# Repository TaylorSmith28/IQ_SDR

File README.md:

# IQ_SDR
The goal of this project was to design a software defined radio (SDR) reciever that operated in the range of 7-12 MHz. This project was conducted with my partner Cadyn Maddocks as part of Walla Walla University's Electronics II course.
## Design Goals
The following design objectives were given for this project:
1. Minimum discernible signal less than 1uV
2. Visible image rejection through quisk
3. Low noise figure
4. Low Cost ($25 budget)
Cadyn Maddocks and I set additional design obectives in order to aid in the design process:
1. Operate in a Frequency Range of 7-12MHz
2. Modulation Type: Short Wave
3. Size of 10 cm by 10 cm
4. Weight of less than 2 pounds
5. Power Requirement of 5V
6. Use of Butterworth Bandpass Filter
7. Use the Raspberry Pi Pico
## Overview
The Software Defined Radio (SDR) reciever has three ports: antenna, USB, and audio jack. The input from the antenna gets filtered, mixed, and then the desired signal is then amplified. The input from the USB to the Raspberry Pi Pico powers the radio and operates the oscillator. The audio jack is connected to a sound card that is attached to a computer where the software demodulates the signal into recognizable audio. Mixing is accomplished via the Raspberry Pi Pico, with ported arduino code from Dr. Rob Frohne. This code interacts with Quisk, a software that controls the reciever through the Raspberry Pi. Quisk should allow the radio to be tuned to certain frequency but this was not accomplished due to issues from porting the arduino code over to the Raspberry Pi Pico. The total cost of this project was about $25.
# Version 6 Design

Shown above is the design schematic for the SDR. More details will be given down below about each section of the schematic. This includes a 12MHz BandPass Filter, Tayloe Mixer, Oscillator, Voltage Smoother, LM4562MA Power Supply, and a Multiple Feedback Lowpass Filter and Amplifier.
## Bandpass Filter

Shown above is a 7-12MHz, 3rd order, series first, Butterworth, bandpass filter. The above filter was designed using the LC Filter Design Tool found here: https://rf-tools.com/lc-filter/
## DC Voltage Smoother

In order to limit noise into our radio a 5V voltage smoother was used before entering the bandpass filter.
## Oscillator

For the design of our radio we used a Si5351A-B-GT Oscillator.
## Tayloe Mixer and Multiple Feedback Lowpass Filter and Amplifer

The SDR uses a SN74CBT3253 Tayloe Mixer that leads into a Multiple Feedback Lowpass Filter and Amplifer. The amplifier employs the use of two LMH4562MA op amps, and has a cutoff frequency around 100kHz.
## Raspberry Pi Pico

Shown above is the Raspberry Pi Pico and the pins used to drive the SDR.
# Simulations
## Multiple Feedback Amplifier Simulation

Shown here is an LTSpice simulation for our Multiple Feedback Amplifier. The simulation shows the amplifier's response between 100Hz to 100MHz.
## 7-12MHz Bandpass Filter

Shown above is a simulation of the 7-12MHz Bandpass Filter. From the simulation, you can see that the response allows signals to pass from approximately 7-12MHz.
# PCB Design

The board shown above was sourced from JLCPCB. Certain design principles were taken into consideration when coming up with the initial design of the board, such as:
1. Avoidance of ground loops
2. Distance between power supply and Antenna
3. Use of a Voltage Smoother
# Quisk Setup
Quisk was downloaded from http://www.james.ahlstrom.name/quisk/ on to a laptop was able to be loaded onto the Raspberry Pi Pico. Quisk was then configured to operating on COM3, the respective port that communicated with the Raspberry Pi. Upon opening Quisk, a new SoftRock Fixed Radio was created and configured to use the appropriate sound card input. The hardware file path was also changed to quisk_conf_openradio.py to use the code that was ported from Dr. Frohne's orignial arduino code.
# Results

Looking at the results above, image rejection can still be seen around 1 microvolt at a 10MHz frequency. This was the best image rejection that we were able to obtain. Using the antenna on top of the Kretschmar roof, we were able to obtain a clearly discernible signal from a religious radio station. Thank the Lord. 
# Credits
Huge credits go to Cadyn Maddocks, my teammate who helped tremendoulsy on this project

Also thanks to Professor Rob Frohne, for without his help this project would not have been possible.

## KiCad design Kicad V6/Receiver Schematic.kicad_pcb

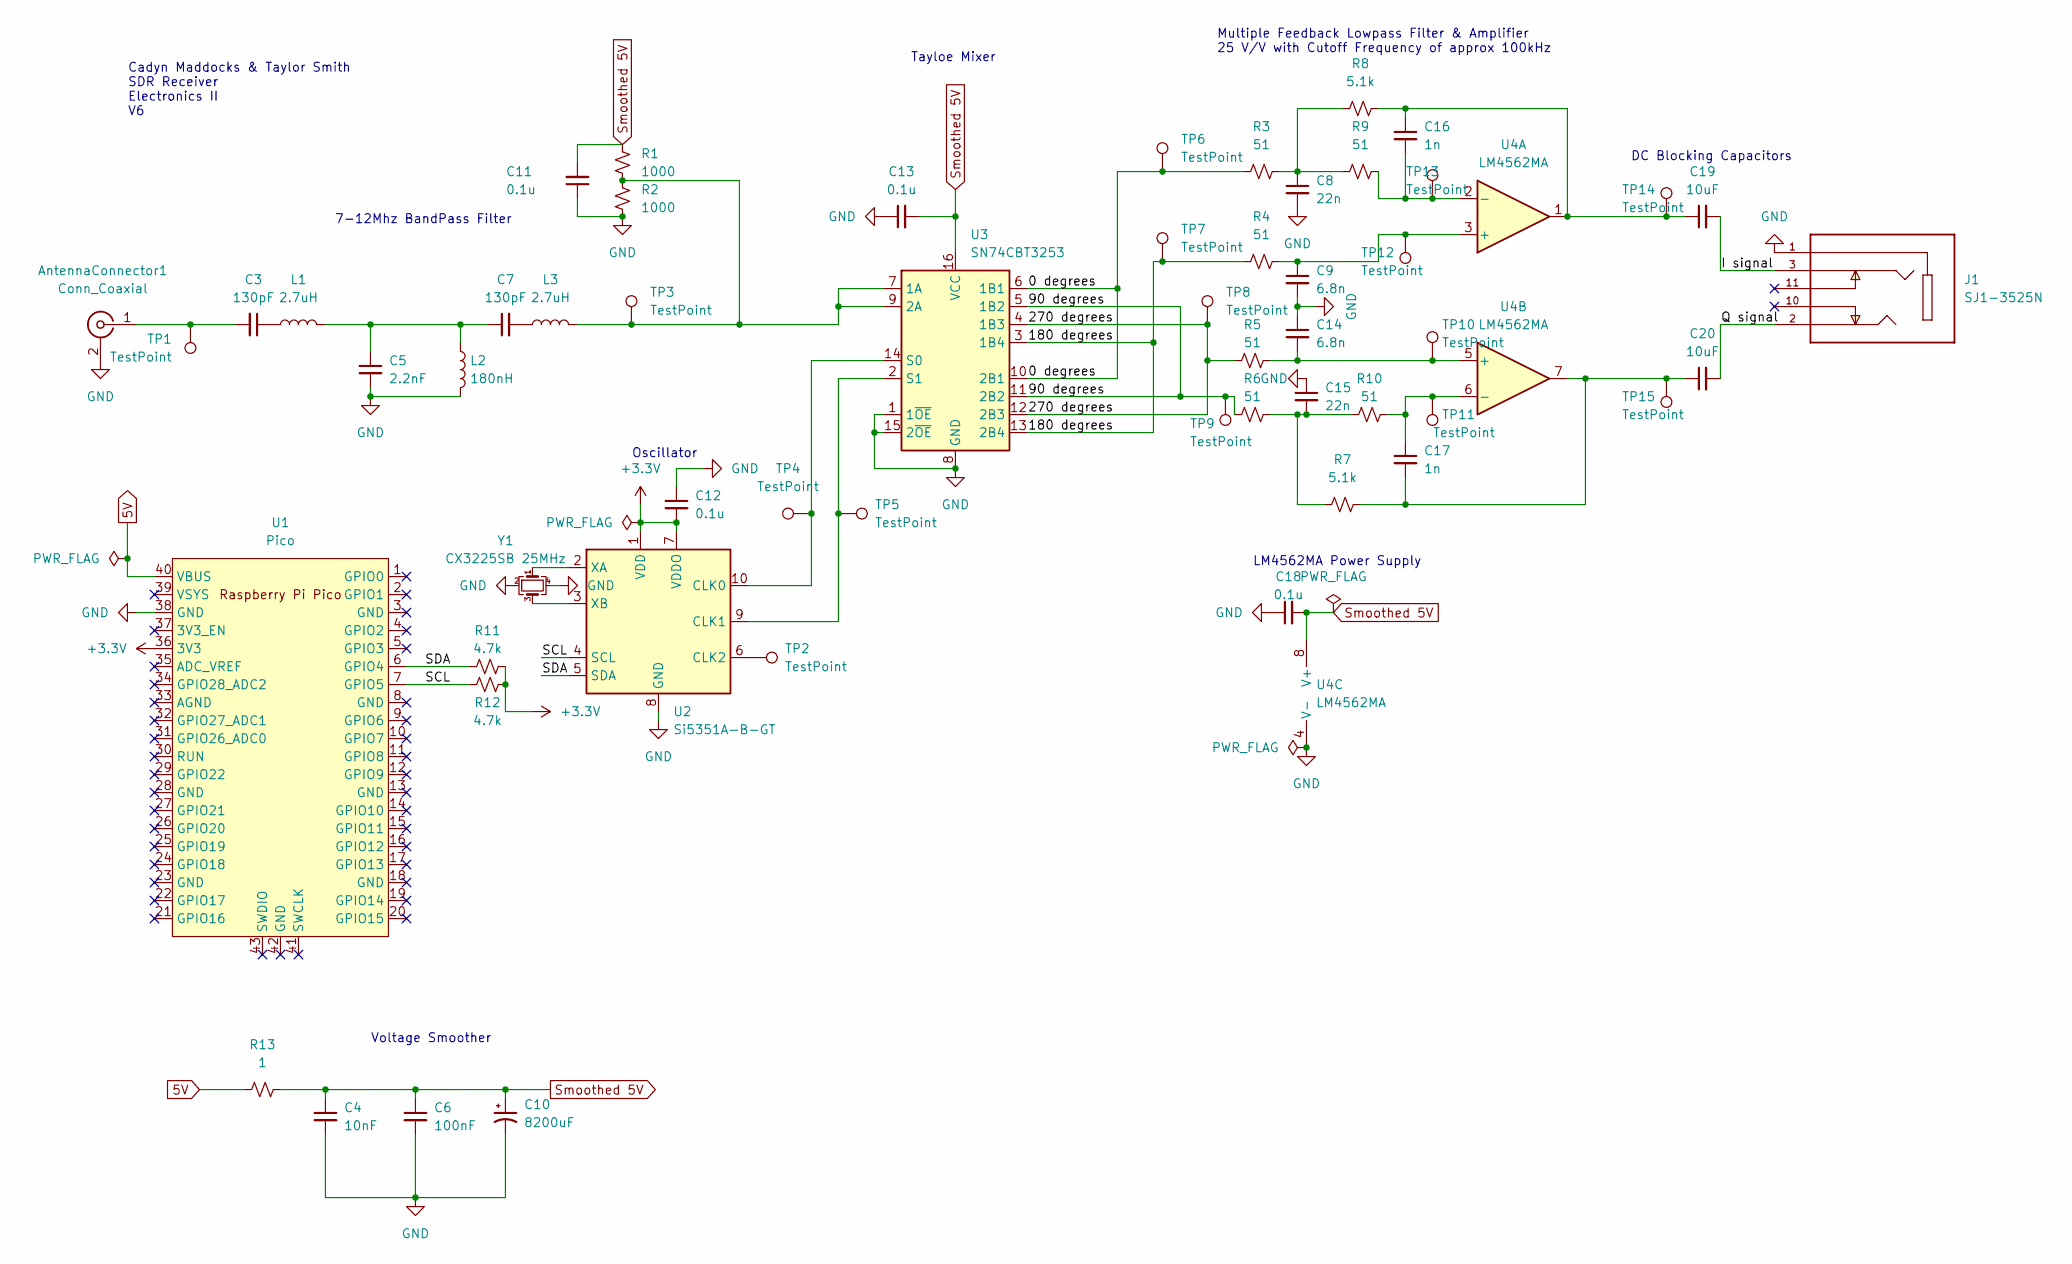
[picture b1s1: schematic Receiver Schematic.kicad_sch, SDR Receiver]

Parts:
AntennaConnector1: Conn_Coaxial; BNC_Amphenol_B6252HB-NPP3G-50_Horizontal
C3, C7: 130pF; C_0805_2012Metric
C4: 10nF; C_0805_2012Metric
C5: 2.2nF; C_0805_2012Metric
C6: 100nF; C_0805_2012Metric
C8, C15: 22n; C_0805_2012Metric
C9, C14: 6.8n; C_0805_2012Metric
C10: 8200uF; CP_Radial_D16.0mm_P7.50mm
C11, C12, C13, C18: 0.1u; C_0805_2012Metric
C16, C17: 1n; C_0805_2012Metric
C19, C20: 10uF; C_0805_2012Metric
J1: SJ1-3525N; CUI_SJ1-3525N; PARTREV 1.02
L1, L3: 2.7uH; L_Toroid_Vertical_L10.0mm_W5.0mm_P5.08mm
L2: 180nH; L_Toroid_Vertical_L10.0mm_W5.0mm_P5.08mm
R1, R2: 1000; R_0805_2012Metric
R3, R4, R5, R6, R9, R10: 51; R_0805_2012Metric
R7, R8: 5.1k; R_0805_2012Metric
R11, R12: 4.7k; R_0805_2012Metric
R13: 1; R_0805_2012Metric
TP1, TP2, TP3, TP4, TP5, TP6, TP7, TP8, TP9, TP10, TP11, TP12, TP13, TP14, TP15: TestPoint; TestPoint_THTPad_2.0x2.0mm_Drill1.0mm
U1: Pico; RPi_Pico_SMD_TH
U2: Si5351A-B-GT; MSOP-10_3x3mm_P0.5mm
U3: SN74CBT3253; SOIC-16_3.9x9.9mm_P1.27mm
U4: LM4562MA; SOIC-8_3.9x4.9mm_P1.27mm
Y1: CX3225SB 25MHz; Crystal_SMD_TXC_7M-4Pin_3.2x2.5mm

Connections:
5V: R13.1, U1.40 (VBUS)
+3V3: C12.2, R11.2, R12.2, U1.36 (3V3), U2.1 (VDD), U2.7 (VDDO)
/0 degrees: R3.1, TP6.1, U3.6 (1B1), U3.10 (2B1)
/90 degrees: R6.1, TP9.1, U3.5 (1B2), U3.11 (2B2)
/180 degrees: R4.1, TP7.1, U3.3 (1B4), U3.13 (2B4)
/270 degrees: R5.1, TP8.1, U3.4 (1B3), U3.12 (2B3)
/I signal: C19.2, J1.3
/Q signal: C20.2, J1.2
/SCL: R12.1, U1.7 (GPIO5), U2.4 (SCL)
/SDA: R11.1, U1.6 (GPIO4), U2.5 (SDA)
GND: AntennaConnector1.2 (Ext), C4.2, C5.2, C6.2, C8.2, C9.2, C10.2, C11.1, C12.1, C13.1, C14.1, C15.1, C18.1, J1.1, L2.2, R2.2, U1.38 (GND), U2.8 (GND), U3.1 (1~OE), U3.8 (GND), U3.15 (2~OE), U4.4 (V-), Y1.2, Y1.4
unnamed: AntennaConnector1.1 (In), C3.2, TP1.1
unnamed: C3.1, L1.1
unnamed: C5.1, C7.1, L1.2, L2.1
unnamed: C7.2, L3.1
unnamed: C8.1, R3.2, R8.1, R9.1
unnamed: C9.1, R4.2, TP12.1, U4.3 (+)
unnamed: C14.2, R5.2, TP10.1, U4.5 (+)
unnamed: C15.2, R6.2, R7.1, R10.1
unnamed: C16.1, C19.1, R8.2, TP14.1, U4.1
unnamed: C16.2, R9.2, TP13.1, U4.2 (-)
unnamed: C17.1, R10.2, TP11.1, U4.6 (-)
unnamed: C17.2, C20.1, R7.2, TP15.1, U4.7
unnamed: L3.2, R1.2, R2.1, TP3.1, U3.7 (1A), U3.9 (2A)
unnamed: TP2.1, U2.6 (CLK2)
unnamed: TP4.1, U2.10 (CLK0), U3.14 (S0)
unnamed: TP5.1, U2.9 (CLK1), U3.2 (S1)
unnamed: U2.2 (XA), Y1.1
unnamed: U2.3 (XB), Y1.3
Smoothed 5V: C4.1, C6.1, C10.1, C11.2, C13.2, C18.2, R1.1, R13.2, U3.16 (VCC), U4.8 (V+)

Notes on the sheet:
Multiple Feedback Lowpass Filter & Amplifier 25 V/V with Cutoff Frequency of approx 100kHz
Oscillator
LM4562MA Power Supply
Tayloe Mixer
7-12Mhz BandPass Filter
DC Blocking Capacitors
Voltage Smoother
Cadyn Maddocks & Taylor Smith SDR Receiver Electronics II V6

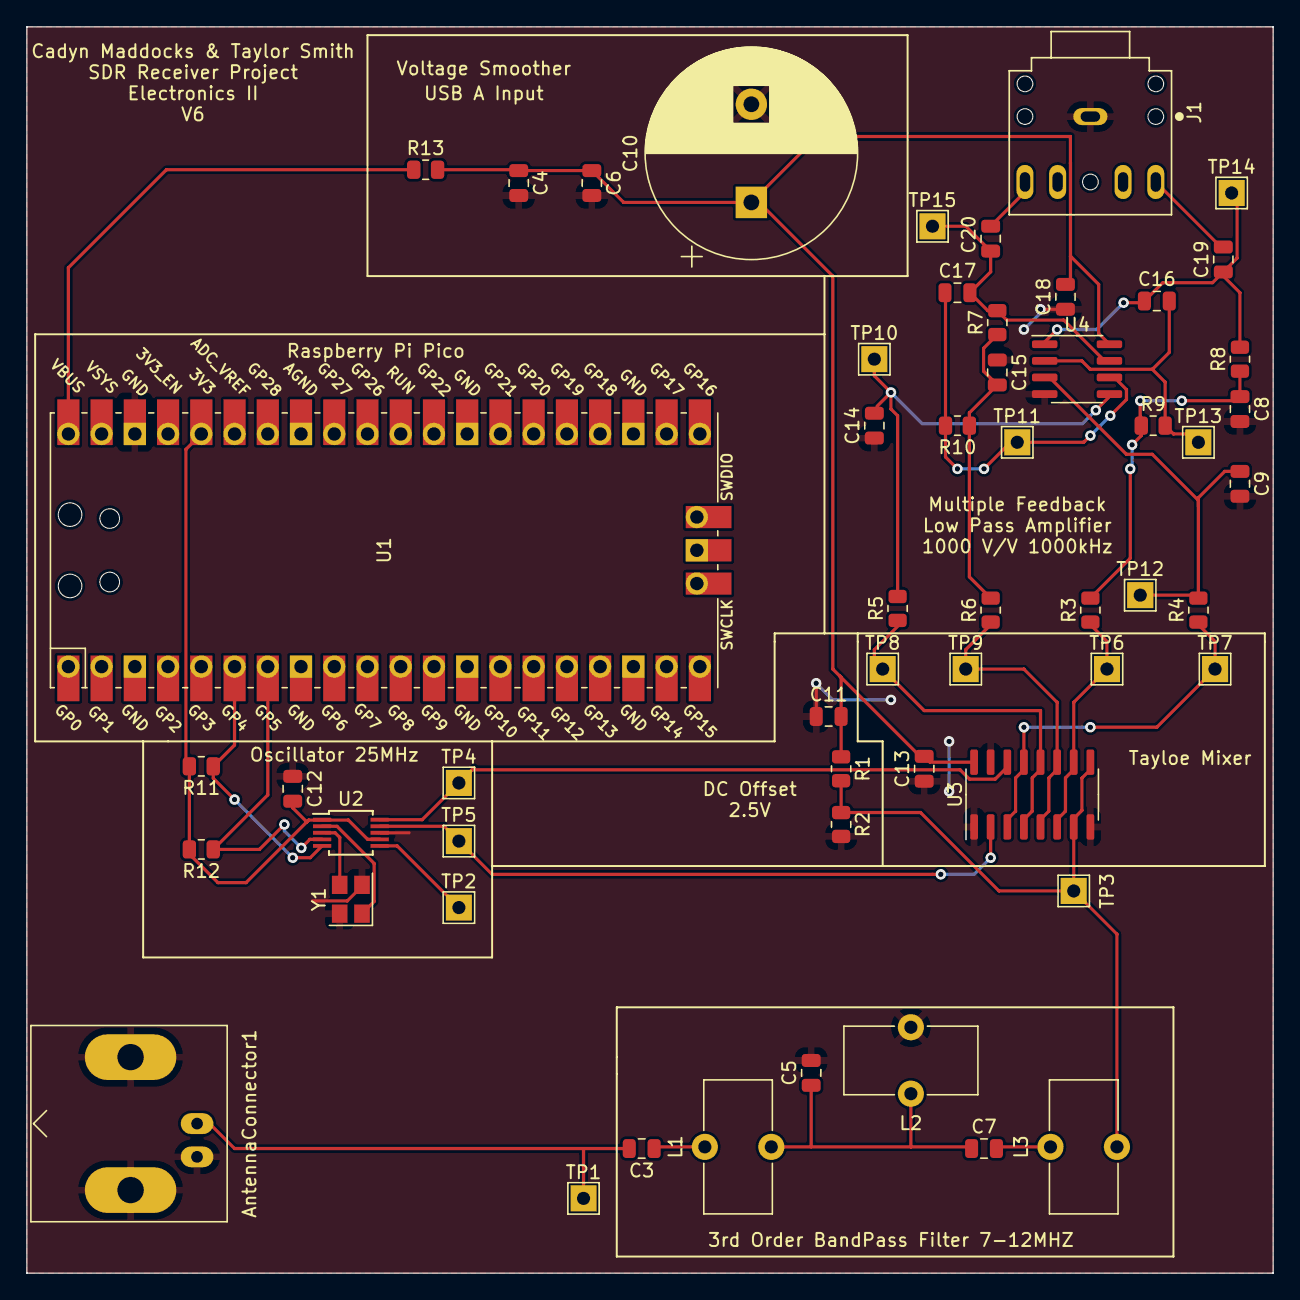
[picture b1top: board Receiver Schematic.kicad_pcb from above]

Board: 2 copper layers, 95.3 x 95.2 mm, 56 parts (0 on the bottom side), 30 nets.

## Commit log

2022-06-07 Files from Project
2022-06-07 Updated Files 2
2022-06-07 Update 3
2022-06-07 Final Commit
